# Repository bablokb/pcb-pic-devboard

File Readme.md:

Development board for PIC12/PIC16 microcontrollers
==================================================

This repository contains the design-files (Kicad) for three PIC12/PIC16
development boards.

PIC-Dev-Board
-------------

This is a full sized dev-board, see directory `pic-dev-board.kicad`:

It supports:

  - a PIC12 or a 20-pin PIC16
  - configurable pullups or LEDs on GP0-GP5
  - two shift-registers with LEDs to output 8-16 bits using two GPs
    (see [project pic-sn74hc595](https://github.com/bablokb/pic-sn74hc595))
  - a LCD1602 attached to the first shift-register
    (see [project pic-hd44780_lcd](https://github.com/bablokb/pic-hd44780_lcd))
  - ICSP programming
  - all pins broken out to connectors (TRISB/TRISC only available for PIC16)
  - a large prototyping-area

PIC12-Dev-PCB
-------------

This is a small dev-board for PIC12 MCUs designed for plugging into a
breadboard, see directory `pic12-dev-pcb`:

It supports:

  - PIC12 in SO-8 package
  - ICSP programming
  - connector for an external SN74HC595-pcb
    (see [project pic-sn74hc595](https://github.com/bablokb/pic-sn74hc595)
  - also usable as I2C-connector
  - power-supply using a small micro-USB-connector breakout
  - connector for power-out (should align with the power-rails of the breadboard)
  - a small prototyping area
  - a small switch (optional)
  - two LEDs (optional)

Minimal Stripboard Version
--------------------------

In the directory `pic12-dev-stripboard.kicad` you find the schema and layout for
a minimal stripboard version:

This is a simple solution for plugging a PIC12 into a breadboard.

This version is not meant for ICSP (in-circuit serial
programming), since it does not have any components to guard the rest of the
circuit during programming.

License
-------

Shield: [![CC BY-SA 4.0][cc-by-sa-shield]][cc-by-sa]

This work is licensed under a
[Creative Commons Attribution-ShareAlike 4.0 International
License][cc-by-sa].

[![CC BY-SA 4.0][cc-by-sa-image]][cc-by-sa]

[cc-by-sa]: http://creativecommons.org/licenses/by-sa/4.0/
[cc-by-sa-image]: https://licensebuttons.net/l/by-sa/4.0/88x31.png
[cc-by-sa-shield]:
https://img.shields.io/badge/License-CC%20BY--SA%204.0-lightgrey.svg

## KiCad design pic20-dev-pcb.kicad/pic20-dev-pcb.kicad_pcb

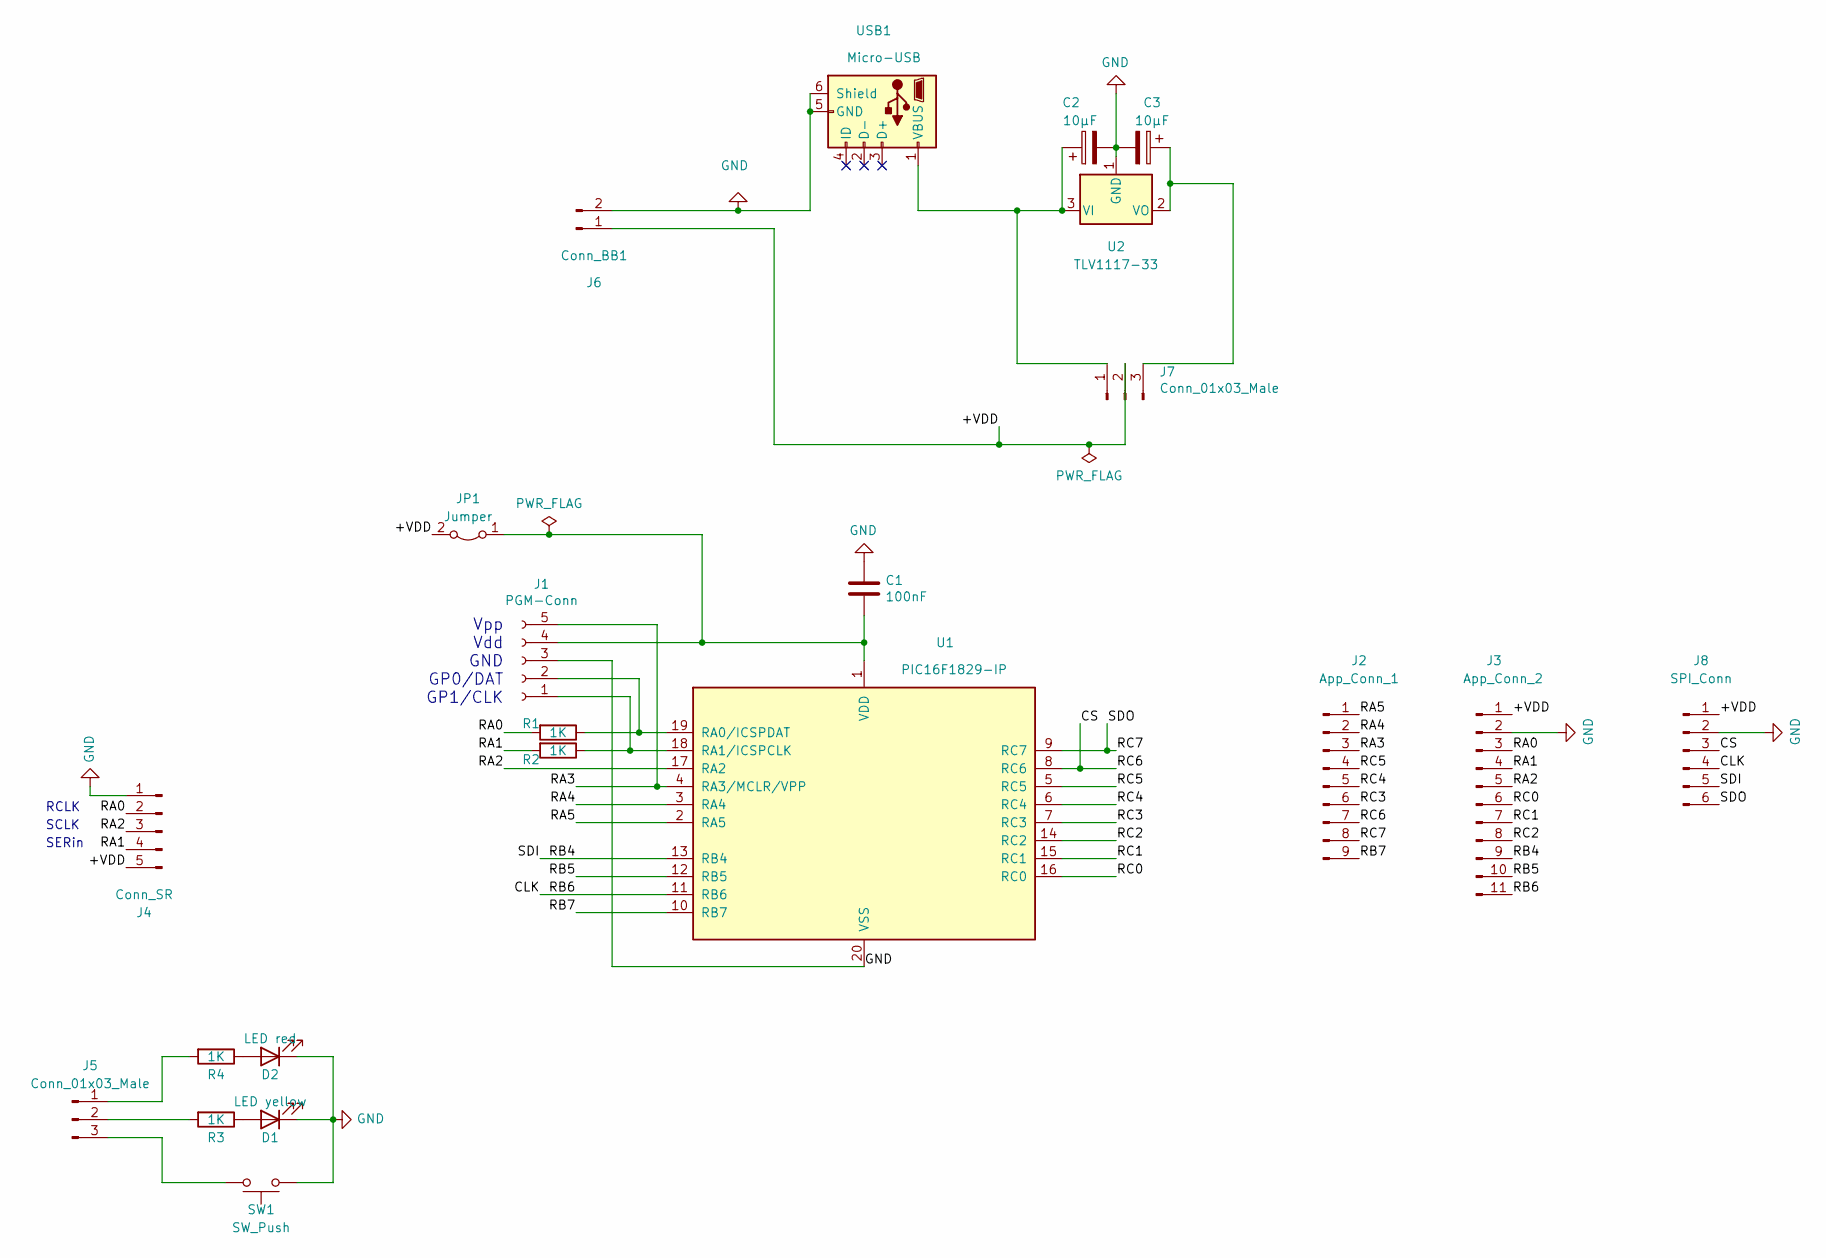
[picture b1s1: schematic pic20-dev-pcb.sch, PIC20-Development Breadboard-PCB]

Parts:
C1: 100nF; C_0805_2012Metric; LCSC C49678
C2, C3: 10µF; CP_EIA-3216-18_Kemet-A; LCSC C7171
D1: LED yellow; LED_0805_2012Metric; LCSC C2296
D2: LED red; LED_0805_2012Metric; LCSC C84256
J1: PGM-Conn; PinSocket_1x05_P2.54mm_Vertical
J2: App_Conn_1; PinHeader_1x09_P2.54mm_Vertical
J3: App_Conn_2; PinHeader_1x11_P2.54mm_Vertical
J4: Conn_SR; PinHeader_1x05_P2.54mm_Vertical
J5, J7: Conn_01x03_Male; PinHeader_1x03_P2.54mm_Vertical
J6: Conn_BB1; PinHeader_1x02_P2.54mm_Vertical
J8: SPI_Conn; PinHeader_1x06_P2.54mm_Vertical
JP1: Jumper; PinHeader_1x02_P2.54mm_Vertical
R1, R2, R3, R4: 1K; R_0805_2012Metric; LCSC C17513
SW1: SW_Push; SW_PUSH_SLIM_1x4
U1: PIC16F1829-IP; DIP-20_W7.62mm_Socket
U2: TLV1117-33; SOT-223; LCSC C6186
USB1: Micro-USB; USB_Micro-B_JLCPCB_40942; LCSC C40942

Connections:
/+VDD: J3.1, J4.5, J6.1, J7.2, J8.1, JP1.2 (B)
/CLK: J3.11, J8.4, U1.11 (RB6)
/CS: J2.7, J8.3, U1.8 (RC6)
/RA0: J3.3, J4.2, R1.2
/RA1: J3.4, J4.4, R2.2
/RA2: J3.5, J4.3, U1.17 (RA2)
/RA3: J1.5, J2.3, U1.4 (RA3/MCLR/VPP)
/RA4: J2.2, U1.3 (RA4)
/RA5: J2.1, U1.2 (RA5)
/RB4: J3.9, J8.5, U1.13 (RB4)
/RB5: J3.10, U1.12 (RB5)
/RB7: J2.9, U1.10 (RB7)
/RC0: J3.6, U1.16 (RC0)
/RC1: J3.7, U1.15 (RC1)
/RC2: J3.8, U1.14 (RC2)
/RC3: J2.6, U1.7 (RC3)
/RC4: J2.5, U1.6 (RC4)
/RC5: J2.4, U1.5 (RC5)
/RC7: J2.8, J8.6, U1.9 (RC7)
GND: C1.1, C2.2, C3.2, D1.1 (K), D2.1 (K), J1.3, J3.2, J4.1, J6.2, J8.2, SW1.2, U1.20 (VSS), U2.1 (GND), USB1.5 (GND), USB1.6 (Shield)
unnamed: C1.2, J1.4, JP1.1 (A), U1.1 (VDD)
unnamed: C2.1, J7.1, U2.3 (VI), USB1.1 (VBUS)
unnamed: C3.1, J7.3, U2.2 (VO)
unnamed: D1.2 (A), R3.1
unnamed: D2.2 (A), R4.1
unnamed: J1.1, R2.1, U1.18 (RA1/ICSPCLK)
unnamed: J1.2, R1.1, U1.19 (RA0/ICSPDAT)
unnamed: J5.1, R4.2
unnamed: J5.2, R3.2
unnamed: J5.3, SW1.1

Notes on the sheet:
Vpp Vdd GND GP0/DAT GP1/CLK
SERin
RCLK
SCLK

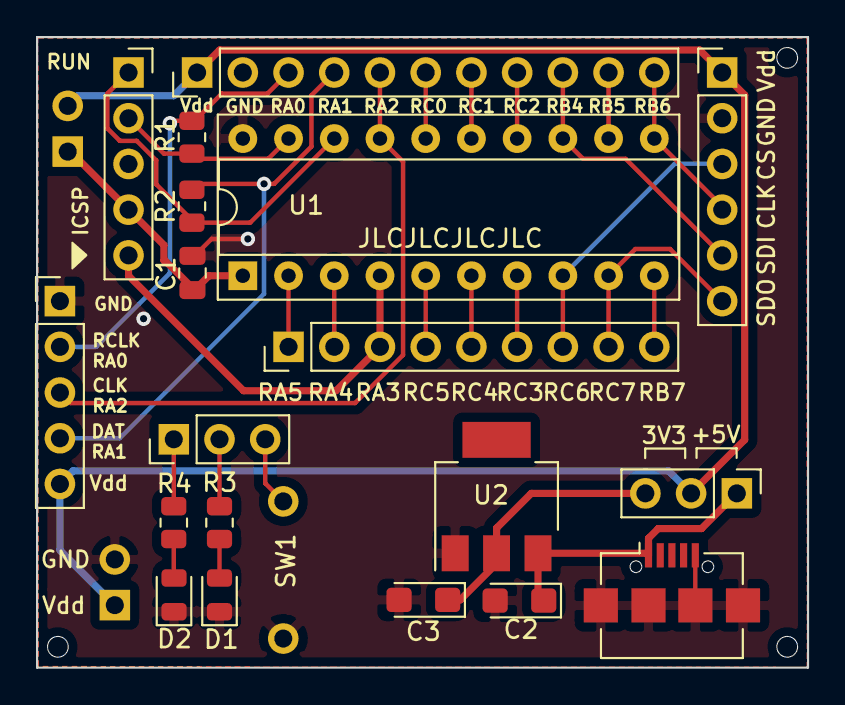
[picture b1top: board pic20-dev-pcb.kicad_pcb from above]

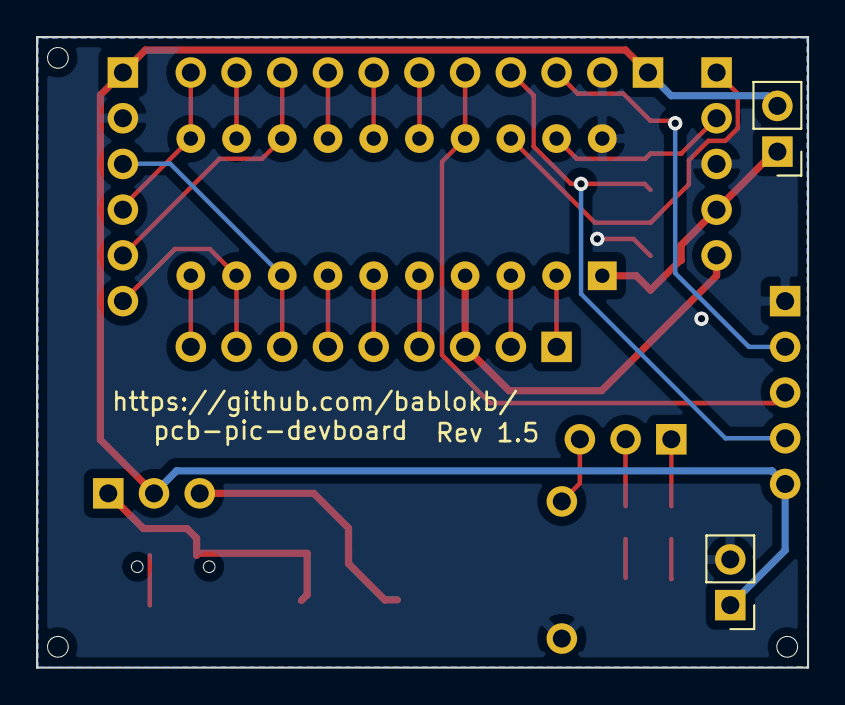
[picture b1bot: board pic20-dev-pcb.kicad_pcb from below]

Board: 2 copper layers, 42.8 x 35.0 mm, 22 parts (2 on the bottom side), 30 nets.

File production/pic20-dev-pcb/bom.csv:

Comment,Designator,Footprint,LCSC
"100nF","C1","Capacitor_SMD:C_0805_2012Metric","C49678"
"10µF","C2,C3","Capacitor_Tantalum_SMD:CP_EIA-3216-18_Kemet-A","C7171"
"LED yellow","D1","LED_SMD:LED_0805_2012Metric","C2296"
"LED red","D2","LED_SMD:LED_0805_2012Metric","C84256"
"PGM-Conn","J1","Connector_PinSocket_2.54mm:PinSocket_1x05_P2.54mm_Vertical",""
"App_Conn_1","J2","Connector_PinHeader_2.54mm:PinHeader_1x09_P2.54mm_Vertical",""
"App_Conn_2","J3","Connector_PinHeader_2.54mm:PinHeader_1x11_P2.54mm_Vertical",""
"Conn_SR","J4","Connector_PinHeader_2.54mm:PinHeader_1x05_P2.54mm_Vertical",""
"Conn_01x03_Male","J5,J7","Connector_PinHeader_2.54mm:PinHeader_1x03_P2.54mm_Vertical",""
"Conn_BB1","J6","Connector_PinHeader_2.54mm:PinHeader_1x02_P2.54mm_Vertical",""
"SPI_Conn","J8","Connector_PinHeader_2.54mm:PinHeader_1x06_P2.54mm_Vertical",""
"Jumper","JP1","Connector_PinHeader_2.54mm:PinHeader_1x02_P2.54mm_Vertical",""
"1K","R1,R2,R3,R4","Resistor_SMD:R_0805_2012Metric","C17513"
"SW_Push","SW1","user:SW_PUSH_SLIM_1x4",""
"PIC16F1829-IP","U1","Package_DIP:DIP-20_W7.62mm_Socket",""
"AMS1117-33","U2","Package_TO_SOT_SMD:SOT-223","C6186"
"Micro-USB","USB1","user:USB_Micro-B_JLCPCB_40942","C40942"

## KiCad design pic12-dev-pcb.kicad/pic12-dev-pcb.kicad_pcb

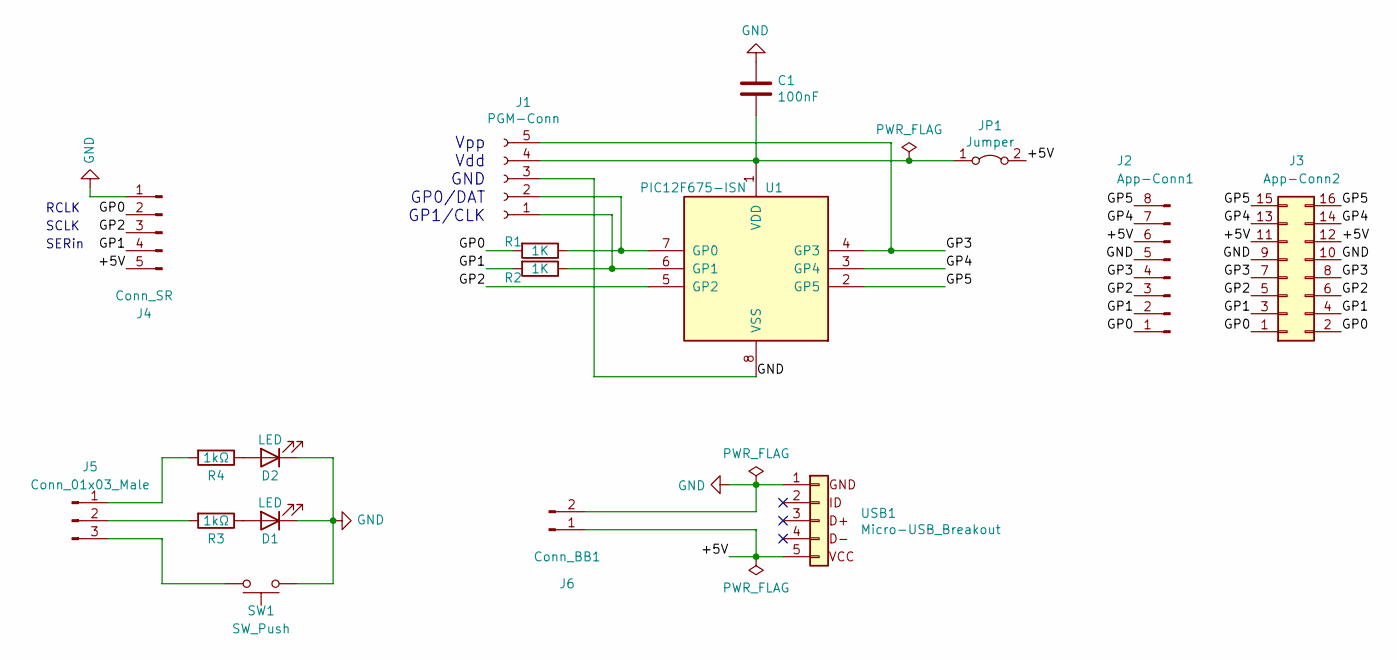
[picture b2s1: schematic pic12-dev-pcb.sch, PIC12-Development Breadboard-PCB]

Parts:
C1: 100nF; C_1206_3216Metric_Pad1.42x1.75mm_HandSolder
D1, D2: LED; LED_1206_3216Metric_Pad1.42x1.75mm_HandSolder
J1: PGM-Conn; PinSocket_1x05_P2.54mm_Vertical
J2: App-Conn1; PinHeader_1x08_P2.54mm_Vertical
J3: App-Conn2; PinHeader_2x08_P2.54mm_Vertical
J4: Conn_SR; PinHeader_1x05_P2.54mm_Vertical
J5: Conn_01x03_Male; PinHeader_1x03_P2.54mm_Vertical
J6: Conn_BB1; PinHeader_1x02_P2.54mm_Vertical
JP1: Jumper; PinHeader_1x02_P2.54mm_Vertical
R1, R2: 1K; R_1206_3216Metric_Pad1.42x1.75mm_HandSolder
R3, R4: 1kΩ; R_1206_3216Metric_Pad1.30x1.75mm_HandSolder
SW1: SW_Push; SW_PUSH_SLIM_1x4
U1: PIC12F675-ISN; SO-8_3.9x4.9mm_P1.27mm_HandSolder
USB1: Micro-USB_Breakout

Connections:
/+5V: J2.6, J3.11, J3.12, J4.5, J6.1, JP1.2 (B), USB1.5
/GP0: J2.1, J3.1, J3.2, J4.2, R1.2
/GP1: J2.2, J3.3, J3.4, J4.4, R2.2
/GP2: J2.3, J3.5, J3.6, J4.3, U1.5 (GP2)
/GP3: J1.5, J2.4, J3.7, J3.8, U1.4 (GP3)
/GP4: J2.7, J3.13, J3.14, U1.3 (GP4)
/GP5: J2.8, J3.15, J3.16, U1.2 (GP5)
GND: C1.1, D1.1 (K), D2.1 (K), J1.3, J2.5, J3.9, J3.10, J4.1, J6.2, SW1.2, U1.8 (VSS), USB1.1
unnamed: C1.2, J1.4, JP1.1 (A), U1.1 (VDD)
unnamed: D1.2 (A), R3.1
unnamed: D2.2 (A), R4.1
unnamed: J1.1, R2.1, U1.6 (GP1)
unnamed: J1.2, R1.1, U1.7 (GP0)
unnamed: J5.1, R4.2
unnamed: J5.2, R3.2
unnamed: J5.3, SW1.1

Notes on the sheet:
Vpp Vdd GND GP0/DAT GP1/CLK
SERin
RCLK
SCLK

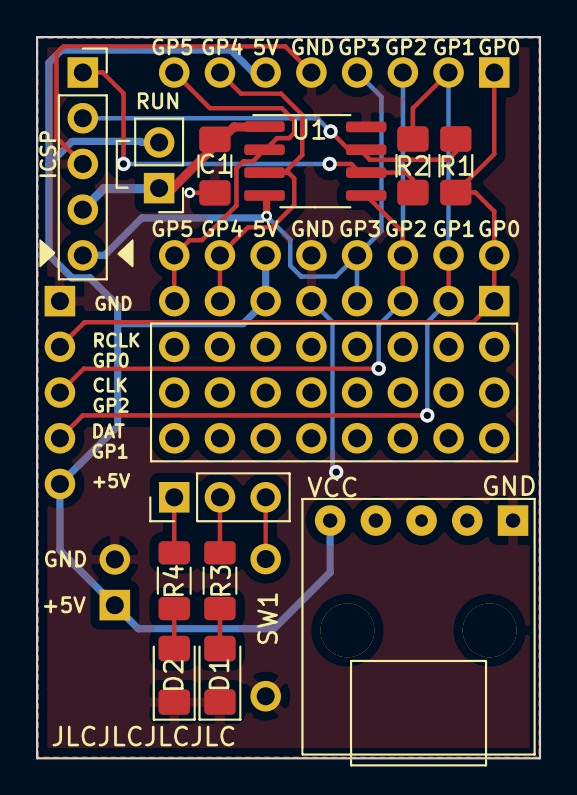
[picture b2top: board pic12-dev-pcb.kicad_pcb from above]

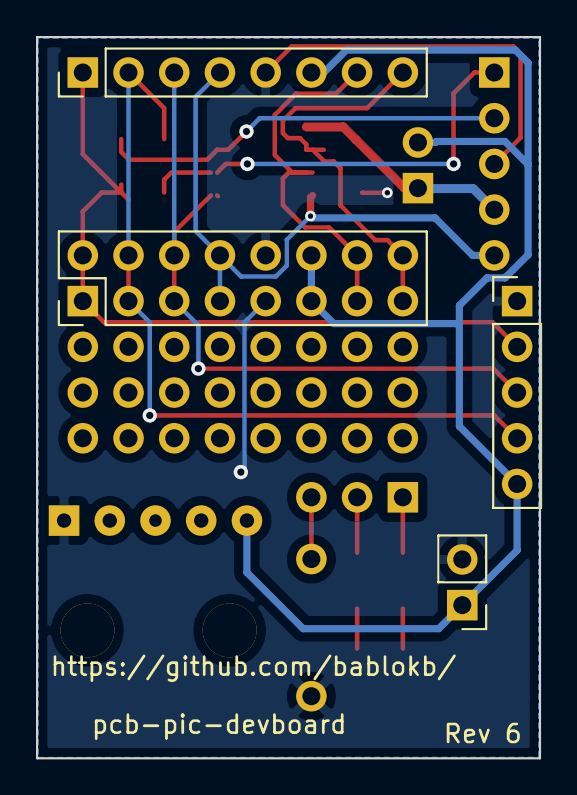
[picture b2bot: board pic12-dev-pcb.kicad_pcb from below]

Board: 2 copper layers, 27.9 x 40.1 mm, 17 parts (4 on the bottom side), 16 nets.

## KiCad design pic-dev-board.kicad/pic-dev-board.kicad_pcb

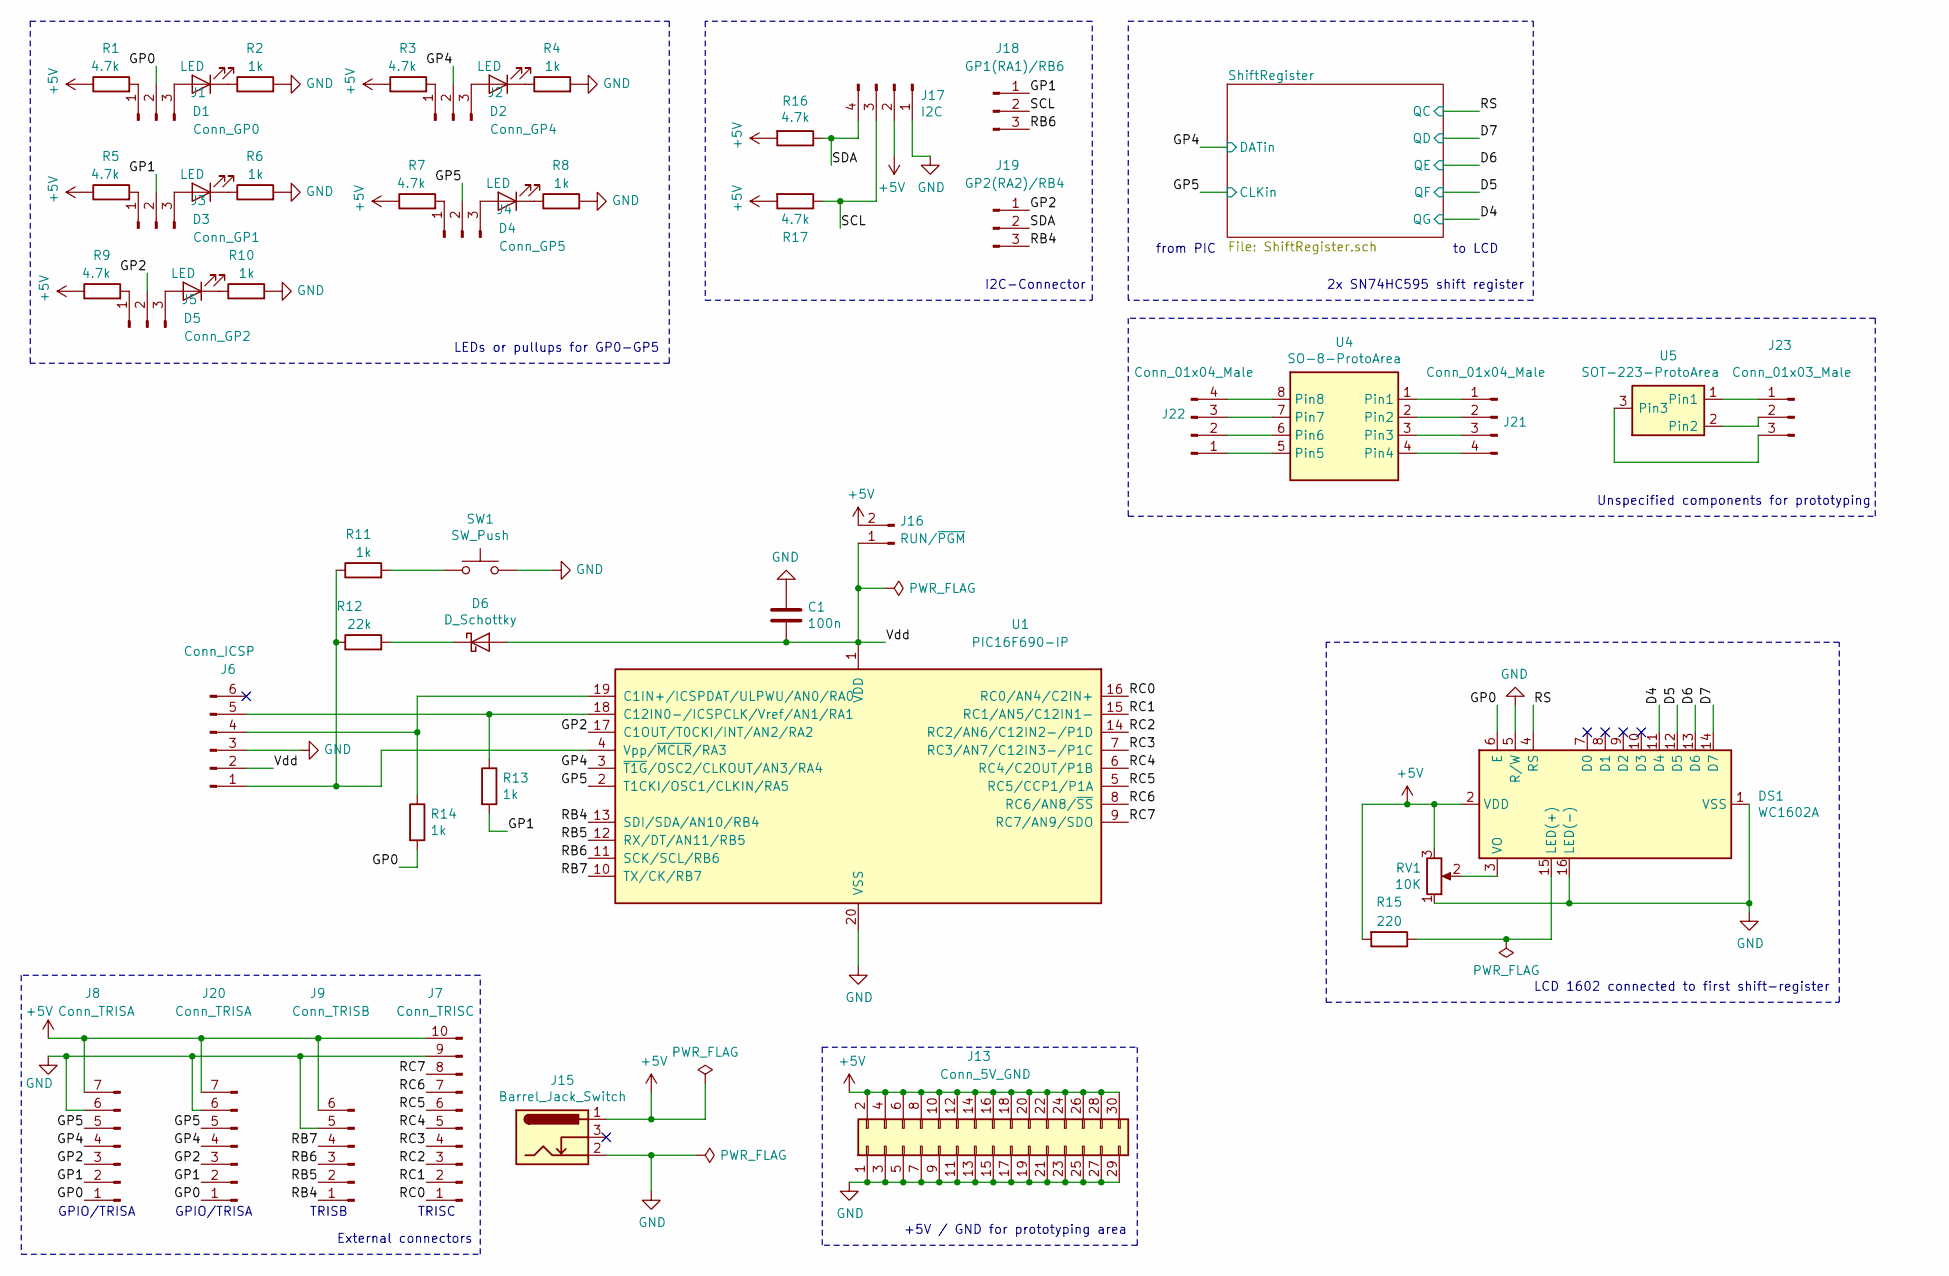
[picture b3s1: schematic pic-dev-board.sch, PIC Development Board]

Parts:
C1: 100n; C_Disc_D3.0mm_W2.0mm_P2.50mm
D1, D2, D3, D4, D5: LED; LED_1206_3216_Pad1.7x1.75mm_BB
D6: D_Schottky; D_A-405_P7.62mm_Horizontal
DS1: WC1602A; WC1602A_Connector
J1: Conn_GP0; PinHeader_1x03_P2.54mm_Vertical
J2: Conn_GP4; PinHeader_1x03_P2.54mm_Vertical
J3: Conn_GP1; PinHeader_1x03_P2.54mm_Vertical
J4: Conn_GP5; PinHeader_1x03_P2.54mm_Vertical
J5: Conn_GP2; PinHeader_1x03_P2.54mm_Vertical
J6: Conn_ICSP; PinHeader_1x06_P2.54mm_Vertical
J7: Conn_TRISC; PinHeader_1x10_P2.54mm_Vertical
J8, J20: Conn_TRISA; PinHeader_1x07_P2.54mm_Vertical
J9: Conn_TRISB; PinHeader_1x06_P2.54mm_Vertical
J13: Conn_5V_GND; PinHeader_2x15_P2.54mm_Vertical_Slim
J15: Barrel_Jack_Switch; BarrelJack_CUI_PJ-102AH_Horizontal
J16: RUN/~PGM; PinHeader_1x02_P2.54mm_Vertical
J17: I2C; PinHeader_1x04_P2.54mm_Vertical
J18: GP1(RA1)/RB6; PinHeader_1x03_P2.54mm_Vertical
J19: GP2(RA2)/RB4; PinHeader_1x03_P2.54mm_Vertical
J21, J22: Conn_01x04_Male; PinHeader_1x04_P2.54mm_Vertical
J23: Conn_01x03_Male; PinHeader_1x03_P2.54mm_Vertical
R1, R3, R5, R7, R9, R16, R17: 4.7k; R_1206_3216_Pad1.7x1.75mm_BB
R2, R4, R6, R8, R10, R11, R13, R14: 1k; R_1206_3216_Pad1.7x1.75mm_BB
R12: 22k; R_1206_3216_Pad1.7x1.75mm_BB
R15: 220; R_1206_3216_Pad1.7x1.75mm_BB
RV1: 10K; TRIM_3362P-1-103
SW1: SW_Push; SW_PUSH_6mm_H9.5mm
U1: PIC16F690-IP; DIP_Socket-20_W4.3_W5.08_W7.62_W10.16_W10.9_3M_220-3342-00-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
U4: SO-8-ProtoArea; SO-8_3.9x4.9mm_P1.27mm
U5: SOT-223-ProtoArea; SOT-223

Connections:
+5V: DS1.2 (VDD), J7.10, J8.7, J9.6, J13.2, J13.4, J13.6, J13.8, J13.10, J13.12, J13.14, J13.16, J13.18, J13.20, J13.22, J13.24, J13.26, J13.28, J13.30, J15.1, J16.2, J17.2, J20.7, R1.1, R3.1, R5.1, R7.1, R9.1, R15.2, R16.2, R17.2, RV1.3; also elsewhere on the board
/D4: DS1.11 (D4); also elsewhere on the board
/D5: DS1.12 (D5); also elsewhere on the board
/D6: DS1.13 (D6); also elsewhere on the board
/D7: DS1.14 (D7); also elsewhere on the board
/GP0: DS1.6 (E), J1.2, J8.1, J20.1, R14.2
/GP1: J3.2, J8.2, J18.1, J20.2, R13.2
/GP2: J5.2, J8.3, J19.1, J20.3, U1.17 (C1OUT/T0CKI/INT/AN2/RA2)
/GP4: J2.2, J8.4, J20.4, U1.3 (~T1G~/OSC2/CLKOUT/AN3/RA4); also elsewhere on the board
/GP5: J4.2, J8.5, J20.5, U1.2 (T1CKI/OSC1/CLKIN/RA5); also elsewhere on the board
/RB4: J9.1, J19.3, U1.13 (SDI/SDA/AN10/RB4)
/RB5: J9.2, U1.12 (RX/DT/AN11/RB5)
/RB6: J9.3, J18.3, U1.11 (SCK/SCL/RB6)
/RB7: J9.4, U1.10 (TX/CK/RB7)
/RC0: J7.1, U1.16 (RC0/AN4/C2IN+)
/RC1: J7.2, U1.15 (RC1/AN5/C12IN1-)
/RC2: J7.3, U1.14 (RC2/AN6/C12IN2-/P1D)
/RC3: J7.4, U1.7 (RC3/AN7/C12IN3-/P1C)
/RC4: J7.5, U1.6 (RC4/C2OUT/P1B)
/RC5: J7.6, U1.5 (RC5/CCP1/P1A)
/RC6: J7.7, U1.8 (RC6/AN8/~SS~)
/RC7: J7.8, U1.9 (RC7/AN9/SDO)
/RS: DS1.4 (RS); also elsewhere on the board
/SCL: J17.3, J18.2, R17.1
/SDA: J17.4, J19.2, R16.1
/Vdd: C1.2, D6.2 (A), J6.2, J16.1, U1.1 (VDD)
GND: C1.1, DS1.1 (VSS), DS1.5 (R/W), DS1.16 (LED(-)), J6.3, J7.9, J8.6, J9.5, J13.1, J13.3, J13.5, J13.7, J13.9, J13.11, J13.13, J13.15, J13.17, J13.19, J13.21, J13.23, J13.25, J13.27, J13.29, J15.2, J17.1, J20.6, R2.2, R4.2, R6.2, R8.2, R10.2, RV1.1, SW1.2, U1.20 (VSS); also elsewhere on the board
unnamed: D1.1 (K), R2.1
unnamed: D1.2 (A), J1.3
unnamed: D2.1 (K), R4.1
unnamed: D2.2 (A), J2.3
unnamed: D3.1 (K), R6.1
unnamed: D3.2 (A), J3.3
unnamed: D4.1 (K), R8.1
unnamed: D4.2 (A), J4.3
unnamed: D5.1 (K), R10.1
unnamed: D5.2 (A), J5.3
unnamed: D6.1 (K), R12.2
unnamed: DS1.3 (VO), RV1.2
unnamed: DS1.15 (LED(+)), R15.1
unnamed: J1.1, R1.2
unnamed: J2.1, R3.2
unnamed: J3.1, R5.2
unnamed: J4.1, R7.2
unnamed: J5.1, R9.2
unnamed: J6.1, R11.1, R12.1, U1.4 (Vpp/~MCLR~/RA3)
unnamed: J6.4, R14.1, U1.19 (C1IN+/ICSPDAT/ULPWU/AN0/RA0)
unnamed: J6.5, R13.1, U1.18 (C12IN0-/ICSPCLK/Vref/AN1/RA1)
unnamed: J21.1, U4.1 (Pin1)
unnamed: J21.2, U4.2 (Pin2)
unnamed: J21.3, U4.3 (Pin3)
unnamed: J21.4, U4.4 (Pin4)
unnamed: J22.1, U4.5 (Pin5)
unnamed: J22.2, U4.6 (Pin6)
unnamed: J22.3, U4.7 (Pin7)
unnamed: J22.4, U4.8 (Pin8)
unnamed: J23.1, U5.1 (Pin1)
unnamed: J23.2, U5.2 (Pin2)
unnamed: J23.3, U5.3 (Pin3)
unnamed: R11.2, SW1.1

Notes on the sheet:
GPIO/TRISA
TRISB
TRISC
I2C-Connector
LEDs or pullups for GP0-GP5
External connectors
LCD 1602 connected to first shift-register
from PIC
to LCD
+5V / GND for prototyping area
2x SN74HC595 shift register
Unspecified components for prototyping

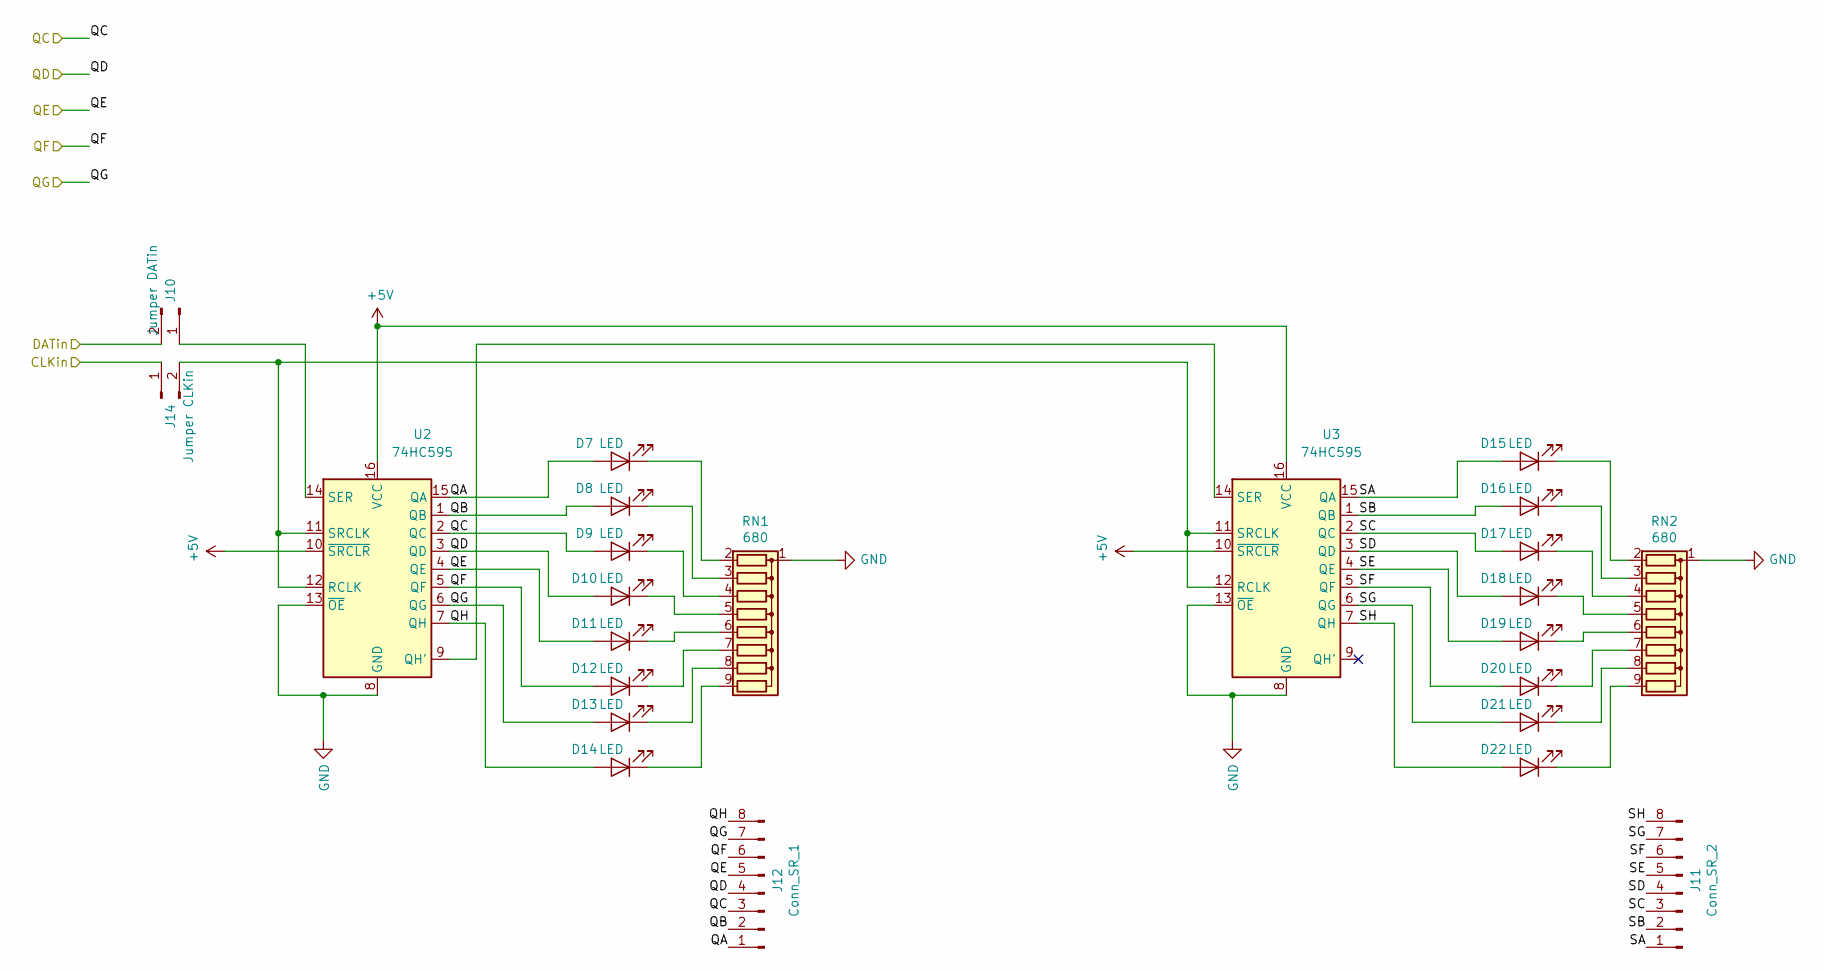
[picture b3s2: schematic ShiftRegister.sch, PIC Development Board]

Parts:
D7, D8, D9, D10, D11, D12, D13, D14, D15, D16, D17, D18, D19, D20, D21, D22: LED; LED_1206_3216_Pad1.7x1.75mm_BB
J10: Jumper DATin; PinHeader_1x02_P2.54mm_Vertical
J11: Conn_SR_2; PinHeader_1x08_P2.54mm_Vertical
J12: Conn_SR_1; PinHeader_1x08_P2.54mm_Vertical
J14: Jumper CLKin; PinHeader_1x02_P2.54mm_Vertical
RN1, RN2: 680; R_Array_SIP9
U2, U3: 74HC595; DIP-16_W7.62mm_Socket

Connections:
+5V: U2.10 (~SRCLR), U2.16 (VCC), U3.10 (~SRCLR), U3.16 (VCC); also elsewhere on the board
/D4: D13.2 (A), J12.7, U2.6 (QG); also elsewhere on the board
/D5: D12.2 (A), J12.6, U2.5 (QF); also elsewhere on the board
/D6: D11.2 (A), J12.5, U2.4 (QE); also elsewhere on the board
/D7: D10.2 (A), J12.4, U2.3 (QD); also elsewhere on the board
/GP4: J10.2; also elsewhere on the board
/GP5: J14.1; also elsewhere on the board
/RS: D9.2 (A), J12.3, U2.2 (QC); also elsewhere on the board
/ShiftRegister/QA: D7.2 (A), J12.1, U2.15 (QA)
/ShiftRegister/QB: D8.2 (A), J12.2, U2.1 (QB)
/ShiftRegister/QH: D14.2 (A), J12.8, U2.7 (QH)
/ShiftRegister/SA: D15.2 (A), J11.1, U3.15 (QA)
/ShiftRegister/SB: D16.2 (A), J11.2, U3.1 (QB)
/ShiftRegister/SC: D17.2 (A), J11.3, U3.2 (QC)
/ShiftRegister/SD: D18.2 (A), J11.4, U3.3 (QD)
/ShiftRegister/SE: D19.2 (A), J11.5, U3.4 (QE)
/ShiftRegister/SF: D20.2 (A), J11.6, U3.5 (QF)
/ShiftRegister/SG: D21.2 (A), J11.7, U3.6 (QG)
/ShiftRegister/SH: D22.2 (A), J11.8, U3.7 (QH)
GND: RN1.1 (common), RN2.1 (common), U2.8 (GND), U2.13 (~OE), U3.8 (GND), U3.13 (~OE); also elsewhere on the board
unnamed: D7.1 (K), RN1.2 (R1)
unnamed: D8.1 (K), RN1.3 (R2)
unnamed: D9.1 (K), RN1.4 (R3)
unnamed: D10.1 (K), RN1.5 (R4)
unnamed: D11.1 (K), RN1.6 (R5)
unnamed: D12.1 (K), RN1.7 (R6)
unnamed: D13.1 (K), RN1.8 (R7)
unnamed: D14.1 (K), RN1.9 (R8)
unnamed: D15.1 (K), RN2.2 (R1)
unnamed: D16.1 (K), RN2.3 (R2)
unnamed: D17.1 (K), RN2.4 (R3)
unnamed: D18.1 (K), RN2.5 (R4)
unnamed: D19.1 (K), RN2.6 (R5)
unnamed: D20.1 (K), RN2.7 (R6)
unnamed: D21.1 (K), RN2.8 (R7)
unnamed: D22.1 (K), RN2.9 (R8)
unnamed: J10.1, U2.14 (SER)
unnamed: J14.2, U2.11 (SRCLK), U2.12 (RCLK), U3.11 (SRCLK), U3.12 (RCLK)
unnamed: U2.9 (QH'), U3.14 (SER)

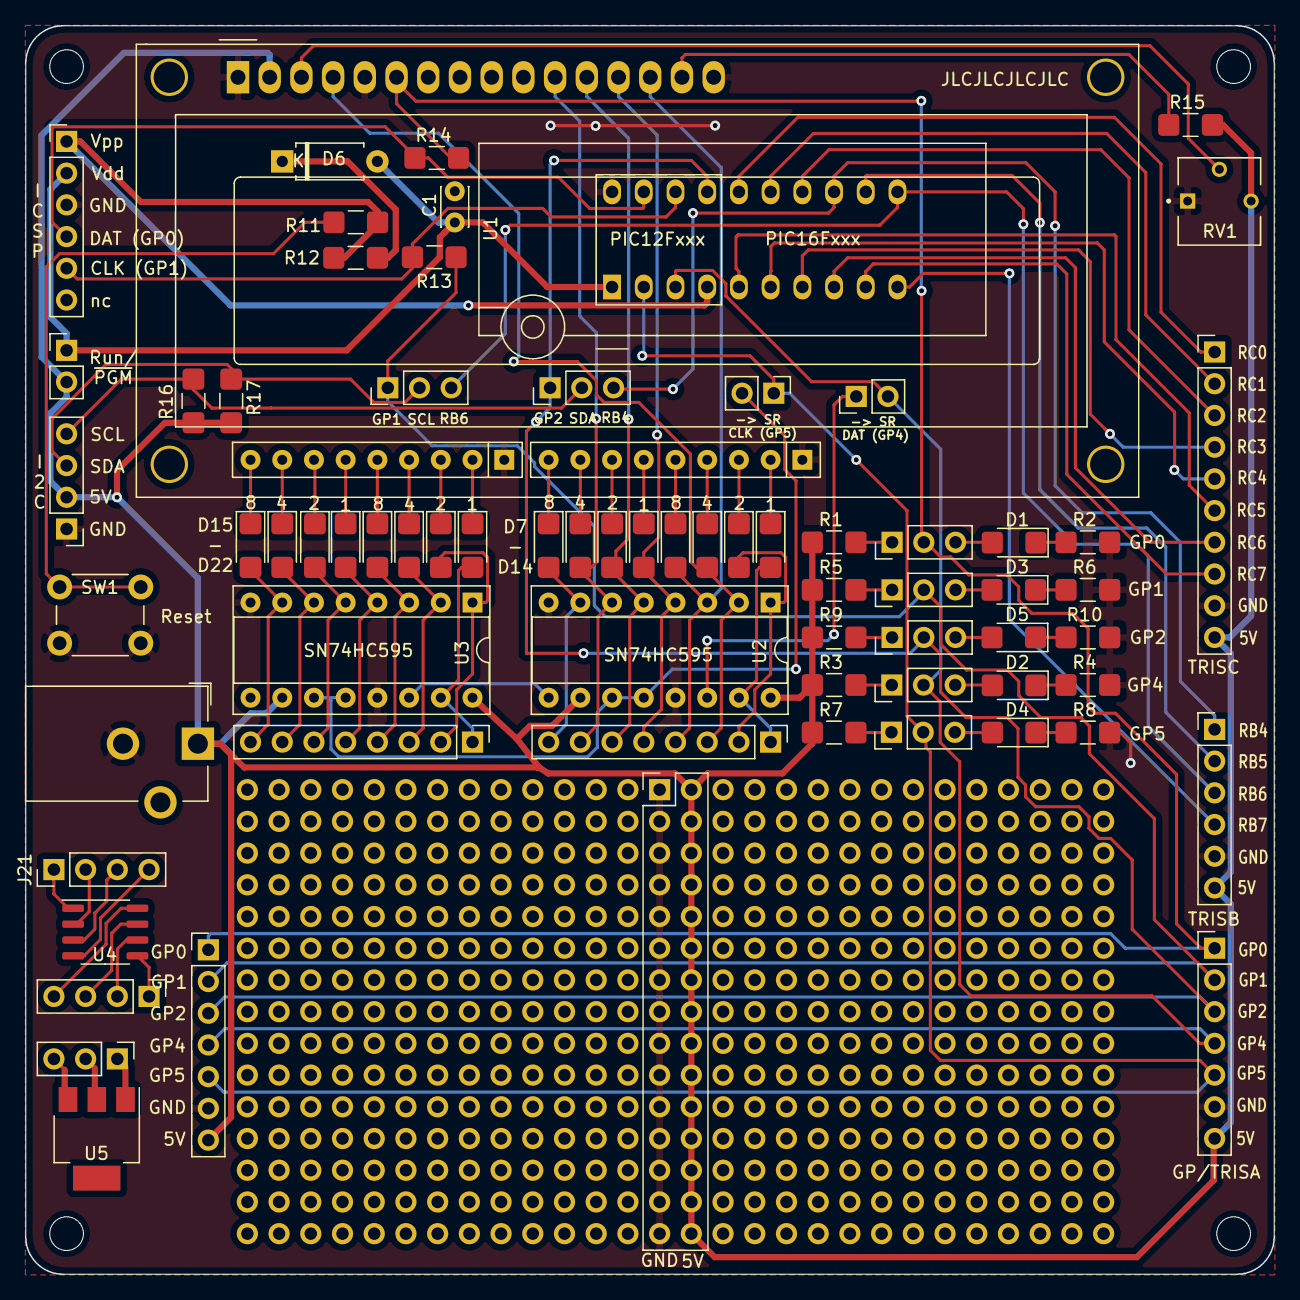
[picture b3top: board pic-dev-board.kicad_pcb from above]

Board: 2 copper layers, 100.0 x 100.0 mm, 73 parts (0 on the bottom side), 90 nets.

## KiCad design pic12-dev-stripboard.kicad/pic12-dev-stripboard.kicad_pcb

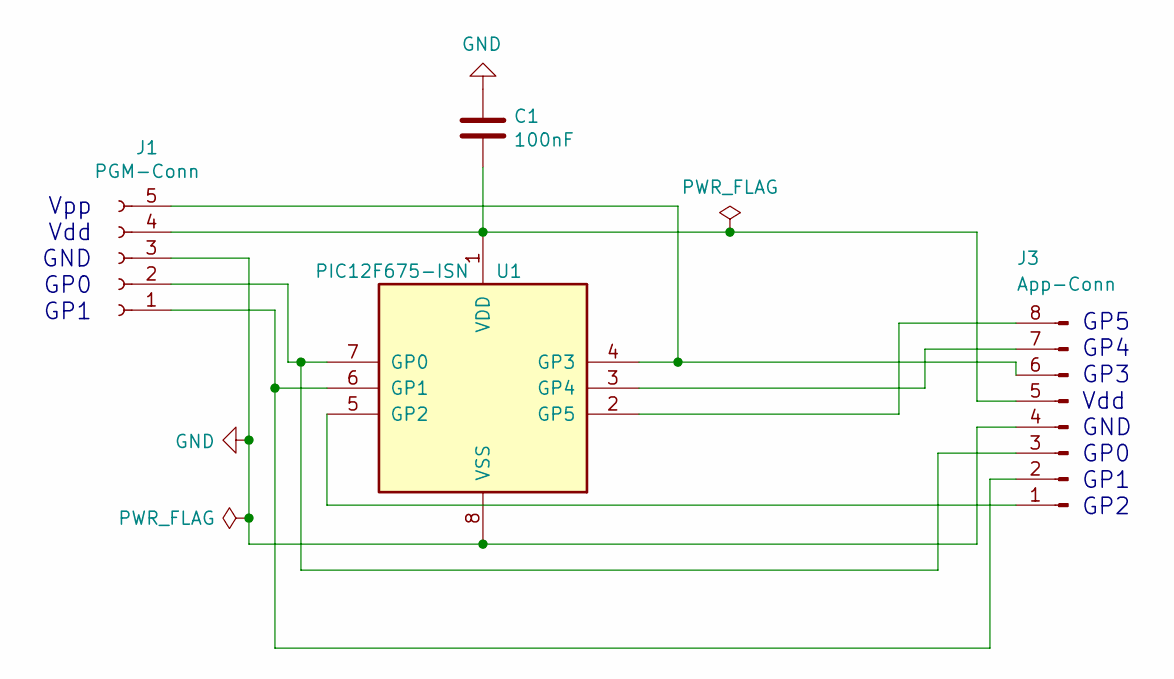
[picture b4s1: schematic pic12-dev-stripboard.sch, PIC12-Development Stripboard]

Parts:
C1: 100nF; C_Disc_D3.8mm_W2.6mm_P2.50mm
J1: PGM-Conn; PinHeader_1x05_P2.54mm_Vertical
J3: App-Conn; PinHeader_1x08_P2.54mm_Vertical
U1: PIC12F675-ISN; DIP-8_W7.62mm

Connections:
GND: C1.1, J1.3, J3.4, U1.8 (VSS)
unnamed: C1.2, J1.4, J3.5, U1.1 (VDD)
unnamed: J1.1, J3.2, U1.6 (GP1)
unnamed: J1.2, J3.3, U1.7 (GP0)
unnamed: J1.5, J3.6, U1.4 (GP3)
unnamed: J3.1, U1.5 (GP2)
unnamed: J3.7, U1.3 (GP4)
unnamed: J3.8, U1.2 (GP5)

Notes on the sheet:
GP5 GP4 GP3 Vdd GND GP0 GP1 GP2
Vpp Vdd GND GP0 GP1

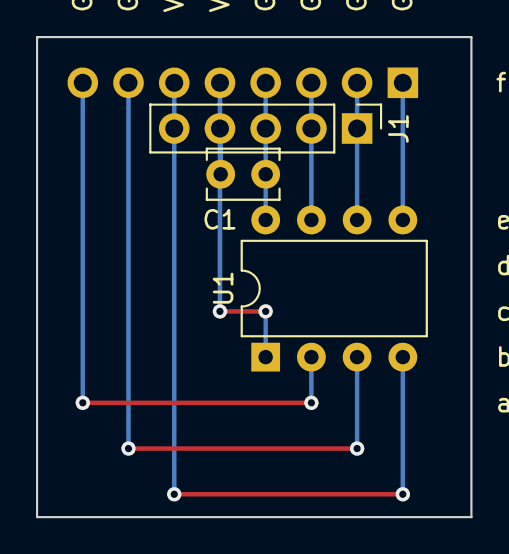
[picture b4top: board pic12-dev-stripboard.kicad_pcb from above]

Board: 2 copper layers, 24.1 x 26.7 mm, 4 parts (1 on the bottom side), 8 nets.

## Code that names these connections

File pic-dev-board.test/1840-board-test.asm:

; 1840-board-test.asm			Steinau, 04.11.2020
; ###########################################################
; Test des 12F1840 auf Bernhards pic-dev-board v. 14.10.20.
; Verwendung interner Osc. / 4 MHz
; 
; Test der LED's der Schiebereg. und RA0-5, außer RA3
; und Ausgabe Bitmuster auf 2x SR595 an RA4,5
;
; Stellung der Jumper auf dem pic-dev-board:
; Run/PGM gesteckt
; Ju GP0,1,2,4,5 jeweils an Pin1-2
; SR: DAT-GP4, CLK-GP5
; I2C: SCL, SDA (Beide Jumper mittig)
;
;
; ###########################################################
;
; Anschlußbelegung:
;
; ICSPDAT,RA0,AN0,		Out LED, alle Pins digital
; ICSPCLK,RA1,AN1,SCL(I2C),	Out LED
;	  RA2,AN2,SDA(I2C),	Out LED
;  /MCLRE,RA3,			Reset
;	  RA4,AN3,		Out LED oder PIN_DATA SR
;	  RA5,			Out LED oder PIN_CLK SR
;	  
; ###########################################################
;	PIC Configuration:

	list		p=12F1840
	#include	<p12f1840.inc>
	movlb	d'0'

; CONFIG PIC12F1840: interner Osc., kein CLKOUT, MCLRE_ON, 
; WDT, PWRT, BOR, CP OFF:

	__CONFIG _CONFIG1, _FOSC_INTOSC & _WDTE_OFF & _PWRTE_OFF & _MCLRE_ON & _CP_OFF & _CPD_OFF & _BOREN_OFF & _CLKOUTEN_OFF
	__CONFIG _CONFIG2, _WRT_OFF & _PLLEN_OFF & _LVP_OFF

; Hexfileformat inhx32 für P12F1840, ok.
; ###########################################################
; EQU's:
	cblock	0x20		; Zeit-UP'e
	miniteil,miditeil,maxiteil,time0,time1,time2,loops,loops2
	endc
;
	cblock	0x30		; SR 595
	srnum,sr8bit,f1,f0
	endc
;
; Verwendung o.g. EQU's:
; srnum : Bitanzahl d. SR595, sr8bit : zu schiebender Wert (SR),
; f1 : High-Wert von 16Bit, f0 : Low-Wert
;
; Definitionen:
;
#define	ledout0	 PORTA,RA0	; LED-OUT für Testzwecke
#define	ledout1	 PORTA,RA1	; LED-OUT für Testzwecke
#define	ledout2	 PORTA,RA2	; LED-OUT für Testzwecke
#define	ledout4	 PORTA,RA4	; LED-OUT für Testzwecke
#define	ledout5	 PORTA,RA5	; LED-OUT für Testzwecke
;
#define PIN_DATA PORTA,RA4	; Signal-Output RA4 (GP4)
#define	PIN_CLK	 PORTA,RA5	; Takt-Output  RA5 (GP5)
;
; ###########################################################
;	org	0x00
	goto	PicInit		; PIC-Initialisierung
;
	org	0x04		; Bank0, für ISR reserviert

; ###########################################################
PicInit
	BANKSEL	PORTA		; Bank0
	clrf	PORTA		; Init PORTA
	clrf	LATA		; PortA u. Latch gelöscht
; alle I/O's Ausgang (TRISA), OSCCON, OSCTUNE (Bank1)
	BANKSEL	TRISA		; Bank1
	clrf	TRISA		; alles Ausgänge

; interner Osc.: OSCCON = 4 MHz (Bank1):
; bit7: SPLLEN=0, bit6-3 IRCF=1101 (4 MHz),
; bit2 U-0, bit1-0=11 Takt vom internen Oscillator Block 
	BANKSEL	OSCCON		; Bank1
	movlw	b'01101011'
	movwf	OSCCON

; Osz.abstimmung factory calibrated TUN<5:0>000000
	BANKSEL	OSCTUNE
	clrf	OSCTUNE

; I/O's digital (ANSELA) (Bank3):
	BANKSEL	ANSELA		; Bank3	
	clrf	ANSELA		; alle Pins digital
;
	movlb	d'0'		; Bank0
;
; ###########################################################
mainx
; 1. Alle PortA-Pins blinken im Sek.-Rythmus:
	movlw	b'00110111'	; alle PortA-Pins=1
	movwf	PORTA
	movlw	d'4'		; 4x250ms = 1s warten
	call	maxitime
;
	movlb	d'0'
	clrf	PORTA	
	movlw	d'4'		; 4x250ms = 1s warten
	call	maxitime
;
; 2. Alle 8 LEDs je SR blinken, wie oben:
	movlw	b'11111111'
	movlb	d'0'
	movwf	f1		; High-Byte SR laden
	movlw	b'11111111'
	movwf	f0		; Low-Byte SR laden
	movf	f1,w		; High-Byte ausgeben
	call	sr595
	movlb	d'0'
	movf	f0,w		; Low-Wert ausgeben
	call	sr595
	call	srtakt1
	movlw	d'4'		; 4x250ms = 1s warten
	call	maxitime
;
	movlb	d'0'
	clrf	f1		; Beide Bytes löschen,
	clrf	f0		; alle LEDs aus
	movf	f1,w		; High-Byte ausgeben
	call	sr595
	movlb	d'0'
	movf	f0,w		; Low-Wert ausgeben
	call	sr595
	call	srtakt1
	movlw	d'4'		; 4x250ms = 1s warten
	call	maxitime
;
	goto	mainx		; Endlosschleife
;
; ###########################################################
; INCLUDE-Dateien:

	#include <quarz_4MHz.asm>	; Warte-UP'e
;	#include <i2c_master_1840.asm>  ; I2C mit MSSP
;	#include <lcdser1bus.asm>	; LCD-Ansteuerungs-UP
;	#include <LCD_Out_1.asm>	; LCD-Ausgaben-UP
	#include <UPsr595.asm>		; Schieberegister-UP

; ###########################################################
; zusätzliche UP'e: 
; ###########################################################

; ############################################################
; UP
; ############################################################


; ###########################################################
	end
; ###########################################################
;
; Programm 1840-board-test.asm

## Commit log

2020-08-11 moved shift-register to hierarchical sheet / completed connections
2020-08-13 updated project description
2020-08-13 added power-connector (barrel-jack)
2020-08-13 added jumper to isolate +5V during programming
2020-08-13 added I2C-connector
2020-08-14 added second shift-register
2020-08-14 added +5V/GND connectors
2020-08-14 added labels, algined parts
2020-08-15 replaced with stripboard.jpg
2020-08-15 link to stripboard.jpg instead of (removed) preview-stripboard.png
2020-08-15 added footprints
2020-08-15 initial commit (outline 10x10cm)
2020-08-16 changed values of connectors
2020-08-17 changed +5V/GND connector
2020-08-17 added +5V/GND to TRIS_* connectorS
2020-08-17 initial pcb-layout, no traces yet
2020-08-18 added ground-planes
2020-08-21 finished traces
2020-08-21 fixed footprint for poti
2020-08-21 updated footprint for +5V/GND connector
2020-08-21 moved reset button and power-connector
2020-08-21 added second GP/TRISA connector
2020-08-21 added footprint for SO-8
2020-08-21 added labels
2020-08-21 Rev1: updated date/revision and added label
2020-08-24 bugfixes: no Vdd connection to barrel-jack, missing connection Vpp to R11/R12
2020-08-24 I2C-connector: swapped SCL/SDA
2020-08-26 removed unnecessary power-flag
2020-08-26 reverting Vdd on barrel-jack, power-flag
2020-08-26 updated to new I2C-layout
2020-08-29 updated revision label
2020-08-29 replaced DIP-socket with textool socket
2020-08-31 added SR-connector
2020-09-04 layout with textool
2020-09-07 fine-tuning of traces
2020-09-07 Rev4: added SO-8/SOT-223 components to schema to prevent DRC-errors on pcb
2020-09-07 Rev 2: different layout, SR connector
2020-09-10 fine-tuning of labels
2020-09-17 place SR-connector, add markers
2020-09-17 fix labeling of GP2 net, add USB-connector
2020-09-19 swap GP0-GP2, add micro-USB breakout
2020-09-22 updated gerber-export options
2020-09-22 added JLC-number field
2020-09-25 changed SO-8 footprint to handsolder-version
2020-09-25 updated footprints, added prototyping area
2020-09-29 move SR-connector to edge
2020-09-29 optimized labels
2020-10-07 updated netlist for pic-dev-board
2020-10-09 minor changes
2020-10-09 added description of pcbs
2020-10-12 added formatting
2020-10-13 bugfix: labels for GP4/GP5 had CLK/DAT swapped
2020-10-23 added link to image of dev-board
2020-10-28 Rev4: fixed order of pins of SR-connector
2020-10-30 Rev5: added GP3 to connectors
2020-10-30 Rev6: added LEDs and button
2020-11-06 changed filenames to have a consistent scheme
2020-11-06 updated links to renamed files
2021-03-12 updated to current version
2021-03-12 updated specs of pic12-dev-pcb
2021-04-21 pic20-dev-pcb: Rev 1.2: use DIP-20 footprint for PIC
2021-04-21 pic20-dev-pcb: Rev 1.3: add SPI-connector, use socket for PIC
2021-04-22 updated footprint for micro-usb
2021-04-26 optimized layout
2021-04-29 pic20-dev-pcb: Rev 1.4: optimizations, prep for production
2021-05-21 Rev 1.5: bugfix Micro-USB connector
2021-10-30 changed LICENSE to CC-BY-SA
2021-10-30 added section about license
2021-10-31 updated with newest production-files
